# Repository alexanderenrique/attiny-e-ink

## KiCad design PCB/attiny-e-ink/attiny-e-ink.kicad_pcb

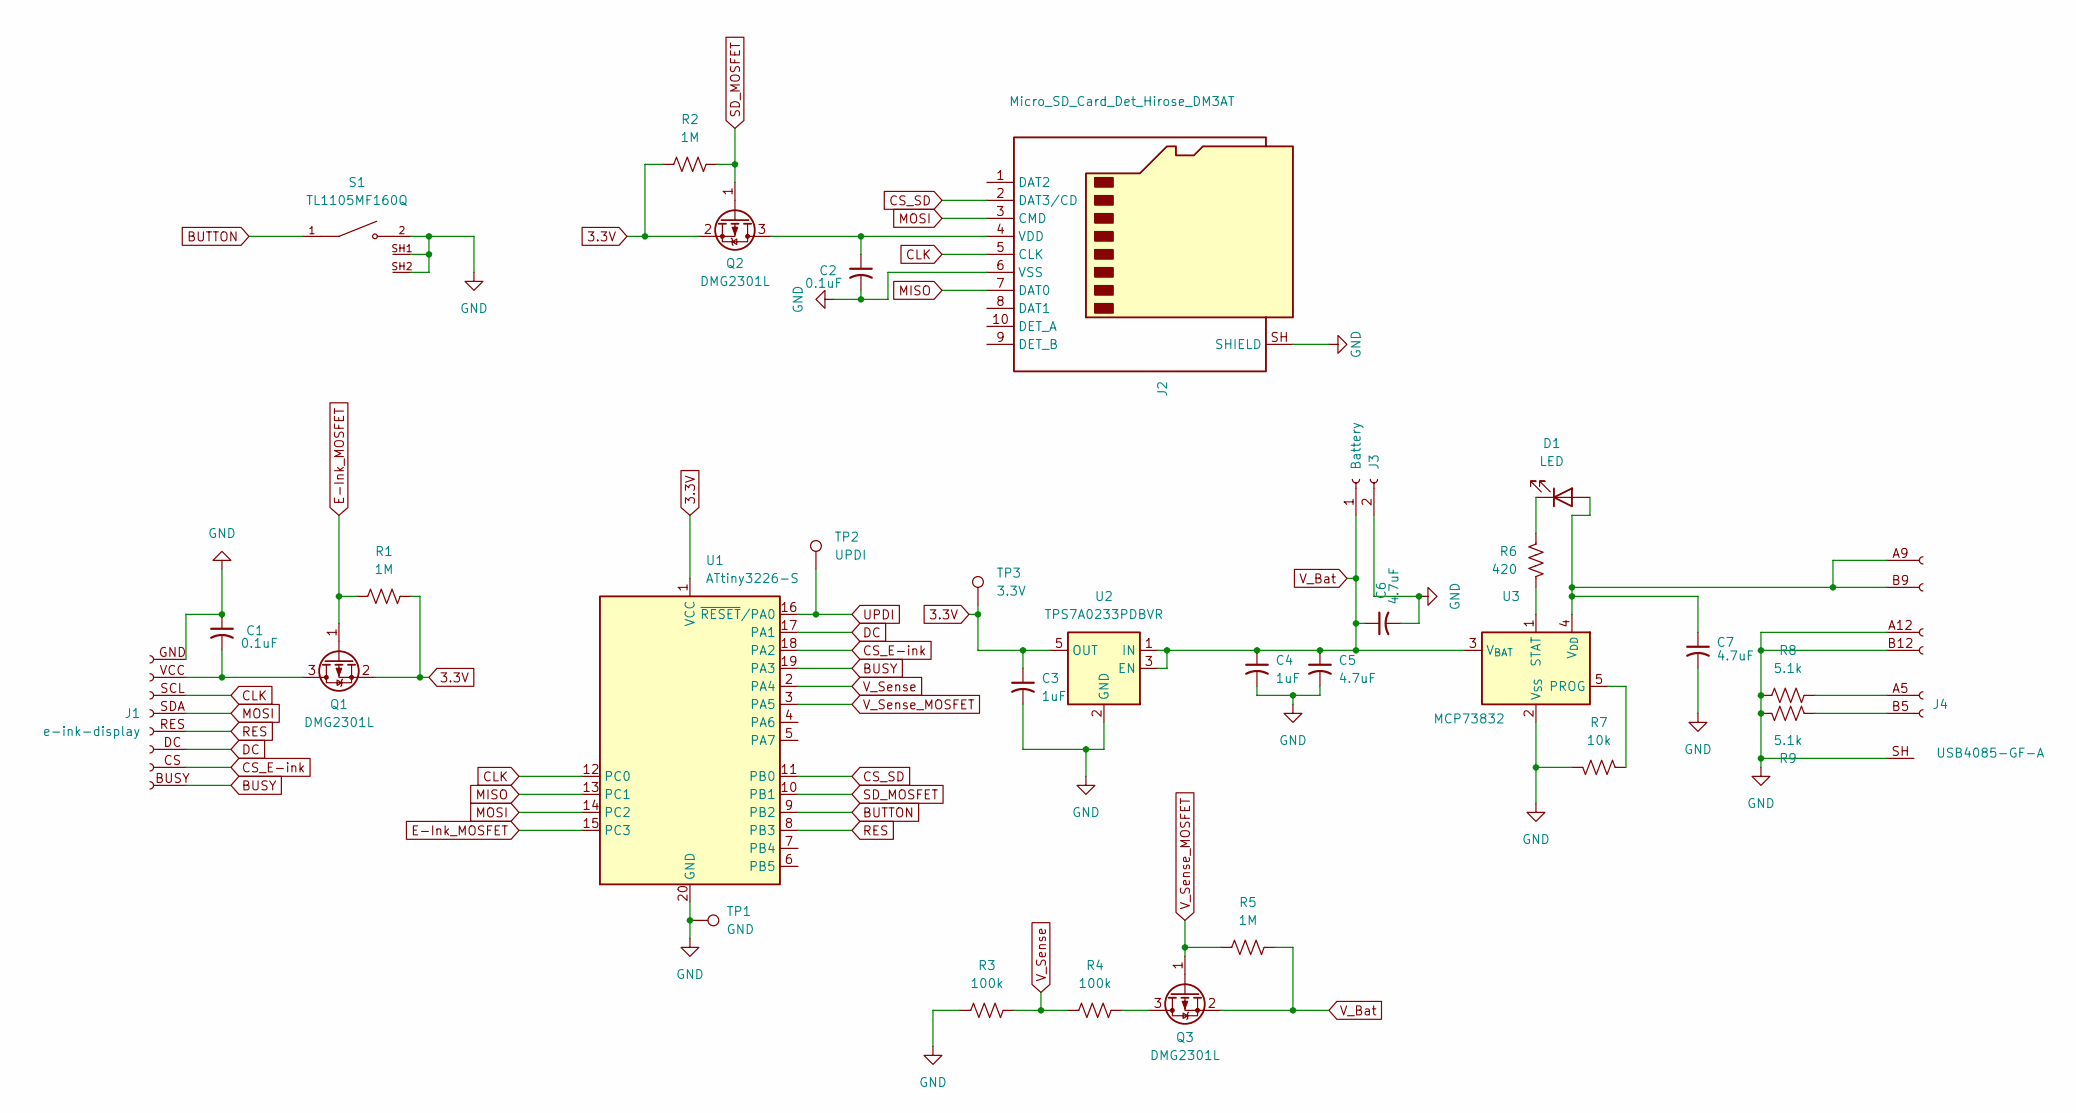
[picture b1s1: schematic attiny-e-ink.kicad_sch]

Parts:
C1, C2: 0.1uF; C_1206_3216Metric
C3, C4: 1uF; C_1206_3216Metric
C5, C6, C7: 4.7uF; C_1206_3216Metric
D1: LED; LED_1206_3216Metric
J1: e-ink-display; PinHeader_1x08_P2.54mm_Vertical
J2: Micro_SD_Card_Det_Hirose_DM3AT; microSD_HC_Hirose_DM3AT-SF-PEJM5
J3: Battery; CONN02_530480210_MOL
J4: USB4085-GF-A; USB_C_Receptacle_GCT_USB4125-xx-x_6P_TopMnt_Horizontal
Q1, Q2, Q3: DMG2301L; SOT-23
R1, R2, R5: 1M; R_1206_3216Metric
R3, R4: 100k; R_1206_3216Metric
R6: 420; R_1206_3216Metric
R7: 10k; R_1206_3216Metric
R8, R9: 5.1k; R_1206_3216Metric
S1: TL1105MF160Q; SW_TL1105MF160Q; PARTREV E
TP1: GND; TestPoint_Pad_D1.5mm
TP2: UPDI; TestPoint_Pad_D1.5mm
TP3: 3.3V; TestPoint_Pad_D1.5mm
U1: ATtiny3226-S; SOIC-20W_7.5x12.8mm_P1.27mm
U2: TPS7A0233PDBVR; SOT-23-5
U3: MCP73832; SOT-23-5

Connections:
3.3V: C3.1, Q1.2 (S), Q2.2 (S), R1.1, R2.2, TP3.1 (1_1), U1.1 (VCC), U2.5 (OUT)
BUSY: J1.BUSY (Pin_8), U1.19 (PA3)
BUTTON: S1.1, U1.9 (PB2)
CLK: J1.SCL (Pin_3), J2.5 (CLK), U1.12 (PC0)
CS_E-ink: J1.CS (Pin_7), U1.18 (PA2)
CS_SD: J2.2 (DAT3/CD), U1.11 (PB0)
DC: J1.DC (Pin_6), U1.17 (PA1)
E-Ink_MOSFET: Q1.1 (G), R1.2, U1.15 (PC3)
GND: C1.1, C2.2, C3.2, C4.2, C5.2, C6.2, C7.2, J1.GND (Pin_1), J2.6 (VSS), J2.SH (SHIELD), J3.2 (Pin_1), J4.A12 (Pin_8), J4.B12 (Pin_10), J4.SH (Pin_10), R3.2, R7.1, R8.2, R9.2, S1.2, S1.SH1, S1.SH2, TP1.1 (1_1), U1.20 (GND), U2.2 (GND), U3.2 (V_{SS})
MISO: J2.7 (DAT0), U1.13 (PC1)
MOSI: J1.SDA (Pin_4), J2.3 (CMD), U1.14 (PC2)
unnamed: C7.1, D1.2 (A), J4.A9 (Pin_2), J4.B9 (Pin_4), U3.4 (V_{DD})
unnamed: D1.1 (K), R6.2
unnamed: C1.2, J1.VCC (Pin_2), Q1.3 (D)
unnamed: C2.1, J2.4 (VDD), Q2.3 (D)
unnamed: J4.A5 (Pin_8), R8.1
unnamed: J4.B5 (Pin_10), R9.1
unnamed: Q3.3 (D), R4.1
unnamed: R7.2, U3.5 (PROG)
unnamed: R6.1, U3.1 (STAT)
RES: J1.RES (Pin_5), U1.8 (PB3)
SD_MOSFET: Q2.1 (G), R2.1, U1.10 (PB1)
UPDI: TP2.1 (1_1), U1.16 (~RESET/PA0)
V_Bat: C4.1, C5.1, C6.1, J3.1 (Pin_2), Q3.2 (S), R5.1, U2.1 (IN), U2.3 (EN), U3.3 (V_{BAT})
V_Sense: R3.1, R4.2, U1.2 (PA4)
V_Sense_MOSFET: Q3.1 (G), R5.2, U1.3 (PA5)

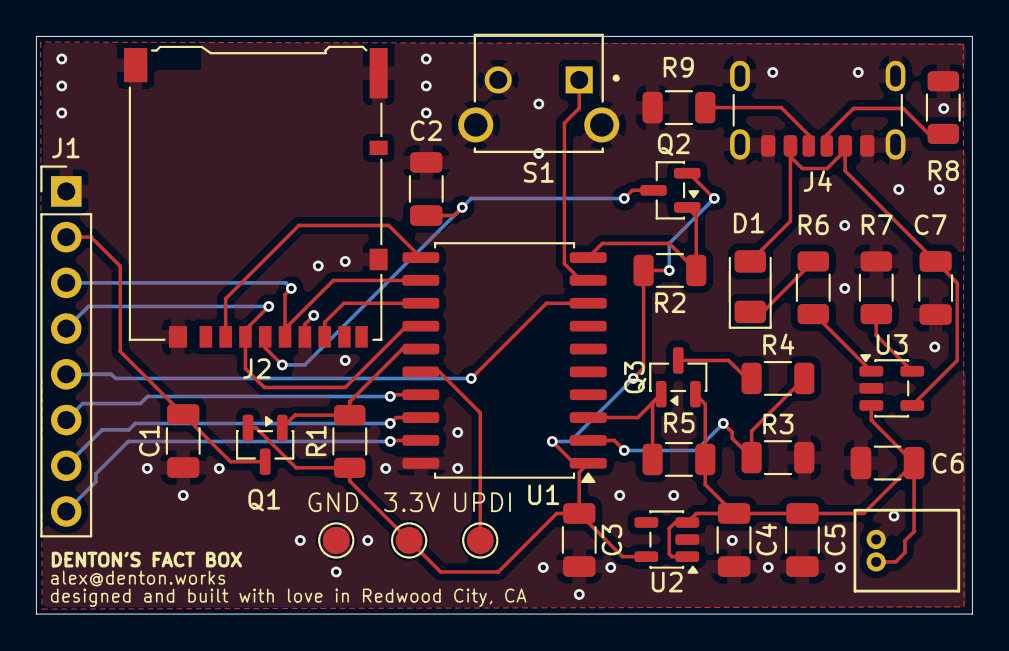
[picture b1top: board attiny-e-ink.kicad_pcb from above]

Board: 2 copper layers, 52.0 x 32.1 mm, 31 parts (0 on the bottom side), 26 nets.

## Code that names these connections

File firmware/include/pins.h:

#pragma once

// Schematic-derived pin map for ATtiny3226 quote display.
// P-channel MOSFETs (DMG2301L): gate LOW = power ON.
// Names avoid megaTinyCore's PIN_SPI_* macros (default SPI on PA1–PA3).

#include <Arduino.h>

// ---------------------------------------------------------------------------
// SPI0 ALT1 — SCK PC0, MISO PC1, MOSI PC2
// PC3 is ALT1 SS but is wired as the e-ink power gate (GPIO).
// ---------------------------------------------------------------------------
static constexpr uint8_t PIN_BUS_SCK  = PIN_PC0;
static constexpr uint8_t PIN_BUS_MISO = PIN_PC1;
static constexpr uint8_t PIN_BUS_MOSI = PIN_PC2;

// ---------------------------------------------------------------------------
// microSD — power gate + CS (active LOW)
// ---------------------------------------------------------------------------
static constexpr uint8_t PIN_SD_PWR = PIN_PB1;  // SD_MOSFET
static constexpr uint8_t PIN_SD_CS  = PIN_PB0;  // CS_SD

// ---------------------------------------------------------------------------
// E-paper (GDEM029C90 / SSD1680)
// ---------------------------------------------------------------------------
static constexpr uint8_t PIN_EPD_PWR  = PIN_PC3;  // E-Ink_MOSFET
static constexpr uint8_t PIN_EPD_CS   = PIN_PA2;  // CS_E-ink
static constexpr uint8_t PIN_EPD_DC   = PIN_PA1;  // DC
static constexpr uint8_t PIN_EPD_RST  = PIN_PB3;  // RES
static constexpr uint8_t PIN_EPD_BUSY = PIN_PA3;  // BUSY (active HIGH)

// ---------------------------------------------------------------------------
// Battery sense — P-FET gate enables divider onto ADC
// Equal resistors (10 kΩ / 10 kΩ): V_Bat = 2 × V_Sense.
// Full cell 4.20 V → 2.10 V at PA4, under the 2.50 V internal ADC reference.
// (R8/R9 are J4 pulldowns, not the divider.)
// ---------------------------------------------------------------------------
static constexpr uint8_t PIN_VSENSE_FET = PIN_PA5;  // V_Sense_MOSFET
static constexpr uint8_t PIN_VSENSE_ADC = PIN_PA4;  // V_Sense (AIN4)
static constexpr uint16_t BATTERY_ADC_REF_MV = 2500;
static constexpr uint16_t BATTERY_ADC_FULL_SCALE = 4096;  // 12-bit, code == Vref

// ---------------------------------------------------------------------------
// User button — active LOW, wakes from power-down
// ---------------------------------------------------------------------------
static constexpr uint8_t PIN_BUTTON = PIN_PB2;

// ---------------------------------------------------------------------------
// Unused GPIO — drive low to avoid floating inputs
// ---------------------------------------------------------------------------
static constexpr uint8_t PIN_UNUSED_PA6 = PIN_PA6;
static constexpr uint8_t PIN_UNUSED_PA7 = PIN_PA7;
static constexpr uint8_t PIN_UNUSED_PB4 = PIN_PB4;
static constexpr uint8_t PIN_UNUSED_PB5 = PIN_PB5;
